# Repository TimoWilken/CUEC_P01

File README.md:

# CUEC_P01_Remote-Controlled Light Switch
This repository contains files for the Electronics Club Remote-Controlled Light Switch project.

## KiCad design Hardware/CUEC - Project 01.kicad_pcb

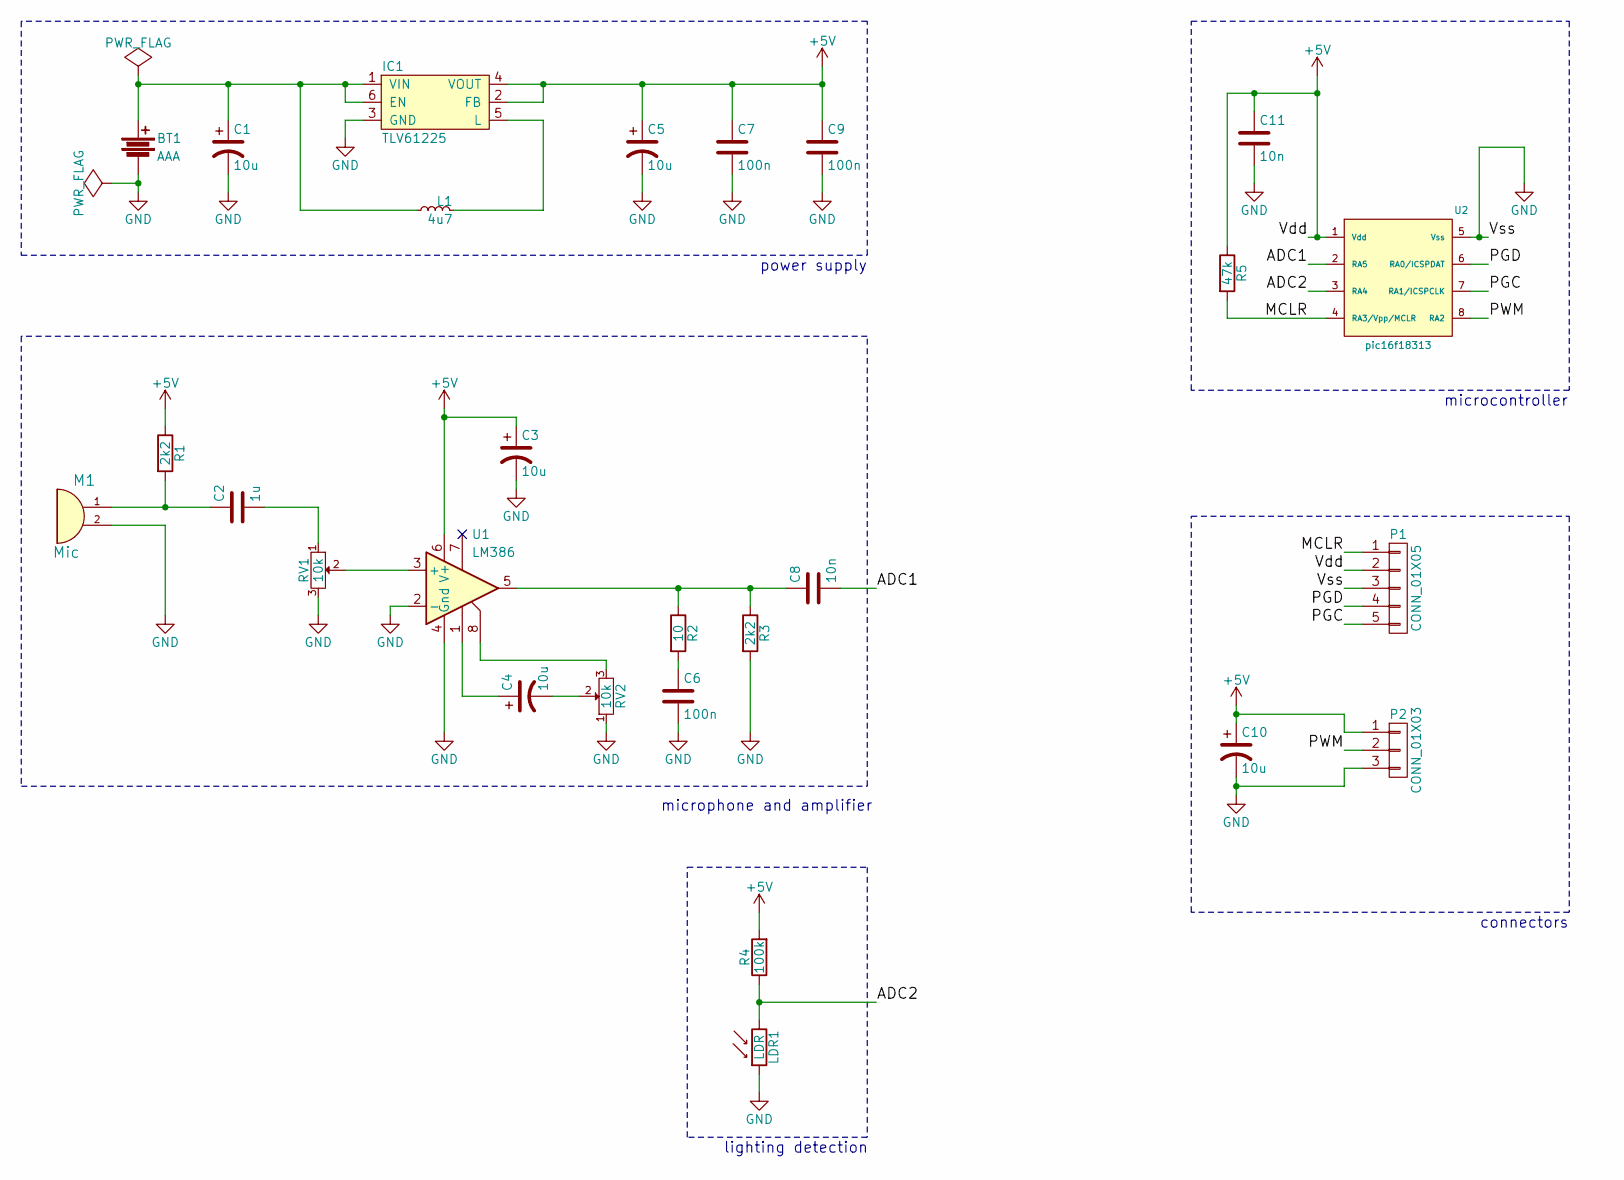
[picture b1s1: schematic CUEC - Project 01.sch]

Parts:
BT1: AAA; AAA_HOLDER; Farnell 1702632
C1, C3, C4, C5, C10: 10u; CP_Radial_D5.0mm_P2.00mm; Farnell 1834168
C2: 1u; C_1206; Farnell 1856632
C6, C7, C9: 100n; C_1206; Farnell 1856599
C8, C11: 10n; C_1206; Farnell 1856566
IC1: TLV61225; SC-70-6; Farnell 2492362
L1: 4u7; 2016M; Farnell 2616849
LDR1: LDR; LDR_NSL_19M51; Farnell 3168335
M1: Mic; Multicomp_Mic_MCKPCM-97H45P-40DB-4808; Farnell 2396073
P1: CONN_01X05; Pin_Header_Straight_1x05_Pitch2.54mm
P2: CONN_01X03; Pin_Header_Straight_1x03_Pitch2.54mm
R1, R3: 2k2; R_1206; Farnell 2447496
R2: 10; R_1206; Farnell 2447457
R4: 100k; R_1206; Farnell 2447453
R5: 47k; R_1206
RV1, RV2: 10k; 3306P-1-103; Farnell 108239
U1: LM386; SOIC-8-N; Farnell 1564701
U2: pic16f18313; SOIC-8-N; Farnell 2810047

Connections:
+5V: C3.1, C5.1, C7.1, C9.1, C10.1, C11.1, IC1.2 (FB), IC1.4 (VOUT), P1.2, P2.1, R1.1, R4.2, R5.1, U1.6 (V+), U2.1 (Vdd)
/ADC1: C8.2, U2.2 (RA5)
/ADC2: LDR1.1, R4.1, U2.3 (RA4)
/MCLR: P1.1, R5.2, U2.4 (RA3/Vpp/MCLR)
/PGC: P1.5, U2.7 (RA1/ICSPCLK)
/PGD: P1.4, U2.6 (RA0/ICSPDAT)
/PWM: P2.2, U2.8 (RA2)
GND: BT1.2, C1.2, C3.2, C5.2, C6.2, C7.2, C9.2, C10.2, C11.2, IC1.3 (GND), LDR1.2, M1.2, P1.3, P2.3, R3.2, RV1.3, RV2.1, U1.2 (-), U1.4 (Gnd), U2.5 (Vss)
unnamed: BT1.1, C1.1, IC1.1 (VIN), IC1.6 (EN), L1.1
unnamed: C2.1, M1.1, R1.2
unnamed: C2.2, RV1.1
unnamed: C4.1, U1.1
unnamed: C4.2, RV2.2
unnamed: C6.1, R2.2
unnamed: C8.1, R2.1, R3.1, U1.5
unnamed: IC1.5 (L), L1.2
unnamed: RV1.2, U1.3 (+)
unnamed: RV2.3, U1.8

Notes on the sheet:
power supply
microphone and amplifier
lighting detection
microcontroller
connectors

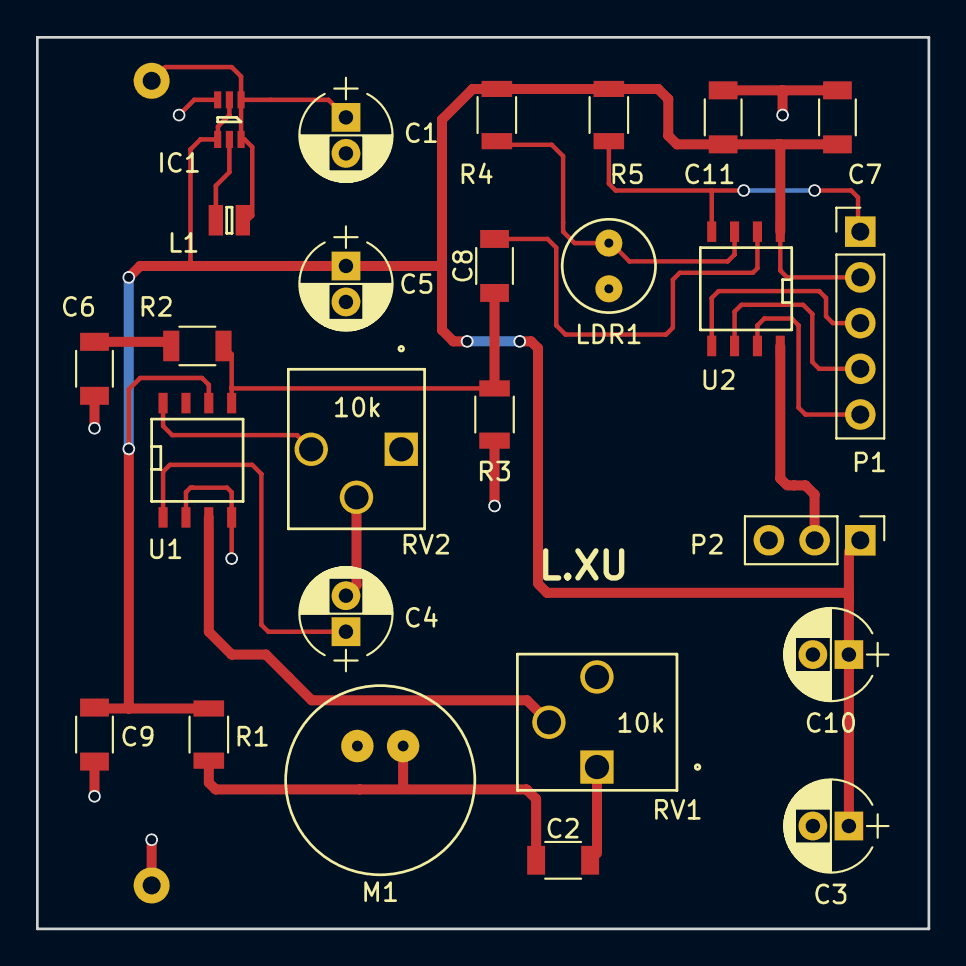
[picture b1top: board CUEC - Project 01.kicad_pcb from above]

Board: 2 copper layers, 49.5 x 49.5 mm, 27 parts (1 on the bottom side), 18 nets.

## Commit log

2018-02-19 Create folder for hardware files
2018-02-19 Add KiCad project files
2018-02-19 Create folder for KiCad library files
2018-02-19 Create folder for KiCad footprint files
2018-02-19 Upload KiCad library files
2018-02-19 Upload KiCad footprint files
2018-02-28 Add first code for microcontroller.
2018-03-19 Add work from meeting.

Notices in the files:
parts and their libraries:
Copyright 2016 Accelerated Designs. All rights reserved.
